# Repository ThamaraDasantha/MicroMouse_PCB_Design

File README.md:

# 🐭 Micromouse Robot – Custom PCB Design

This repository contains the **custom PCB design** for a Micromouse autonomous maze-solving robot. The design was inspired by the **Green Giant Micromouse**, a popular open-source project, and has been tailored to support modular, scalable, and competition-ready robotic development.

---

## 📦 Project Summary

Micromouse robots are small autonomous vehicles designed to solve mazes as quickly as possible. This PCB is the main controller board for such a robot, integrating motor drivers, sensors, power management, and microcontroller components in a compact footprint.

This design builds upon the **Green Giant Micromouse** architecture, with improvements for component sourcing, layout optimization, and modularity for further development.

---

## 🧠 Features & Specifications

| Category               | Description                                               |
|------------------------|-----------------------------------------------------------|
| **Microcontroller**    | STM32F4 / STM32F1 series (footprint supports both)        |
| **Motor Drivers**      | DRV8833 Dual H-Bridge for 2 DC motors                     |
| **Sensors**            | IR distance sensors (front, left, right, 45 digree) – 5 sensors |
| **Power System**       | 2-cell Li-ion with step-down regulator (5V and 3.3V rails)|
| **Connectivity**       | Serial debug headers, encoder inputs, IR TX/RX support    |
| **Form Factor**        | Compact 2-layer PCB, optimized for wheel/motor layout     |
| **Reference Design**   | Based on Green Giant Micromouse with custom adaptations   |

---

## 📐 PCB Design Overview

- Designed using **Eagle**
- Two-layer layout with clear separation of power and logic
- Silkscreen indicators for debugging and easy assembly
- Power and signal decoupling capacitors for noise stability
- Modular connector options for plugging in sensors and actuators

---

## 🧪 Testing & Next Steps

- Motor driver tested with small DC gear motors (30:1)
- Voltage rails tested with onboard regulators (5V and 3.3V)
- IR sensors and encoders interfaced with STM32 test code
- Future integration: PID motor control, maze-solving algorithm, IMU

---

## 📝 Acknowledgment

This design is heavily inspired by the [Green Giant Micromouse](https://github.com/davidtavarez/green-giant) project and adapted for educational and competitive use.

---

## 👨‍💻 Author

**Thamara Banneheka**  
Embedded Systems & Robotics Enthusiast  
📧 thamaradasantha@gmail.com  
🔗 [LinkedIn](https://www.linkedin.com/in/thamara-dasantha-banneheka/)

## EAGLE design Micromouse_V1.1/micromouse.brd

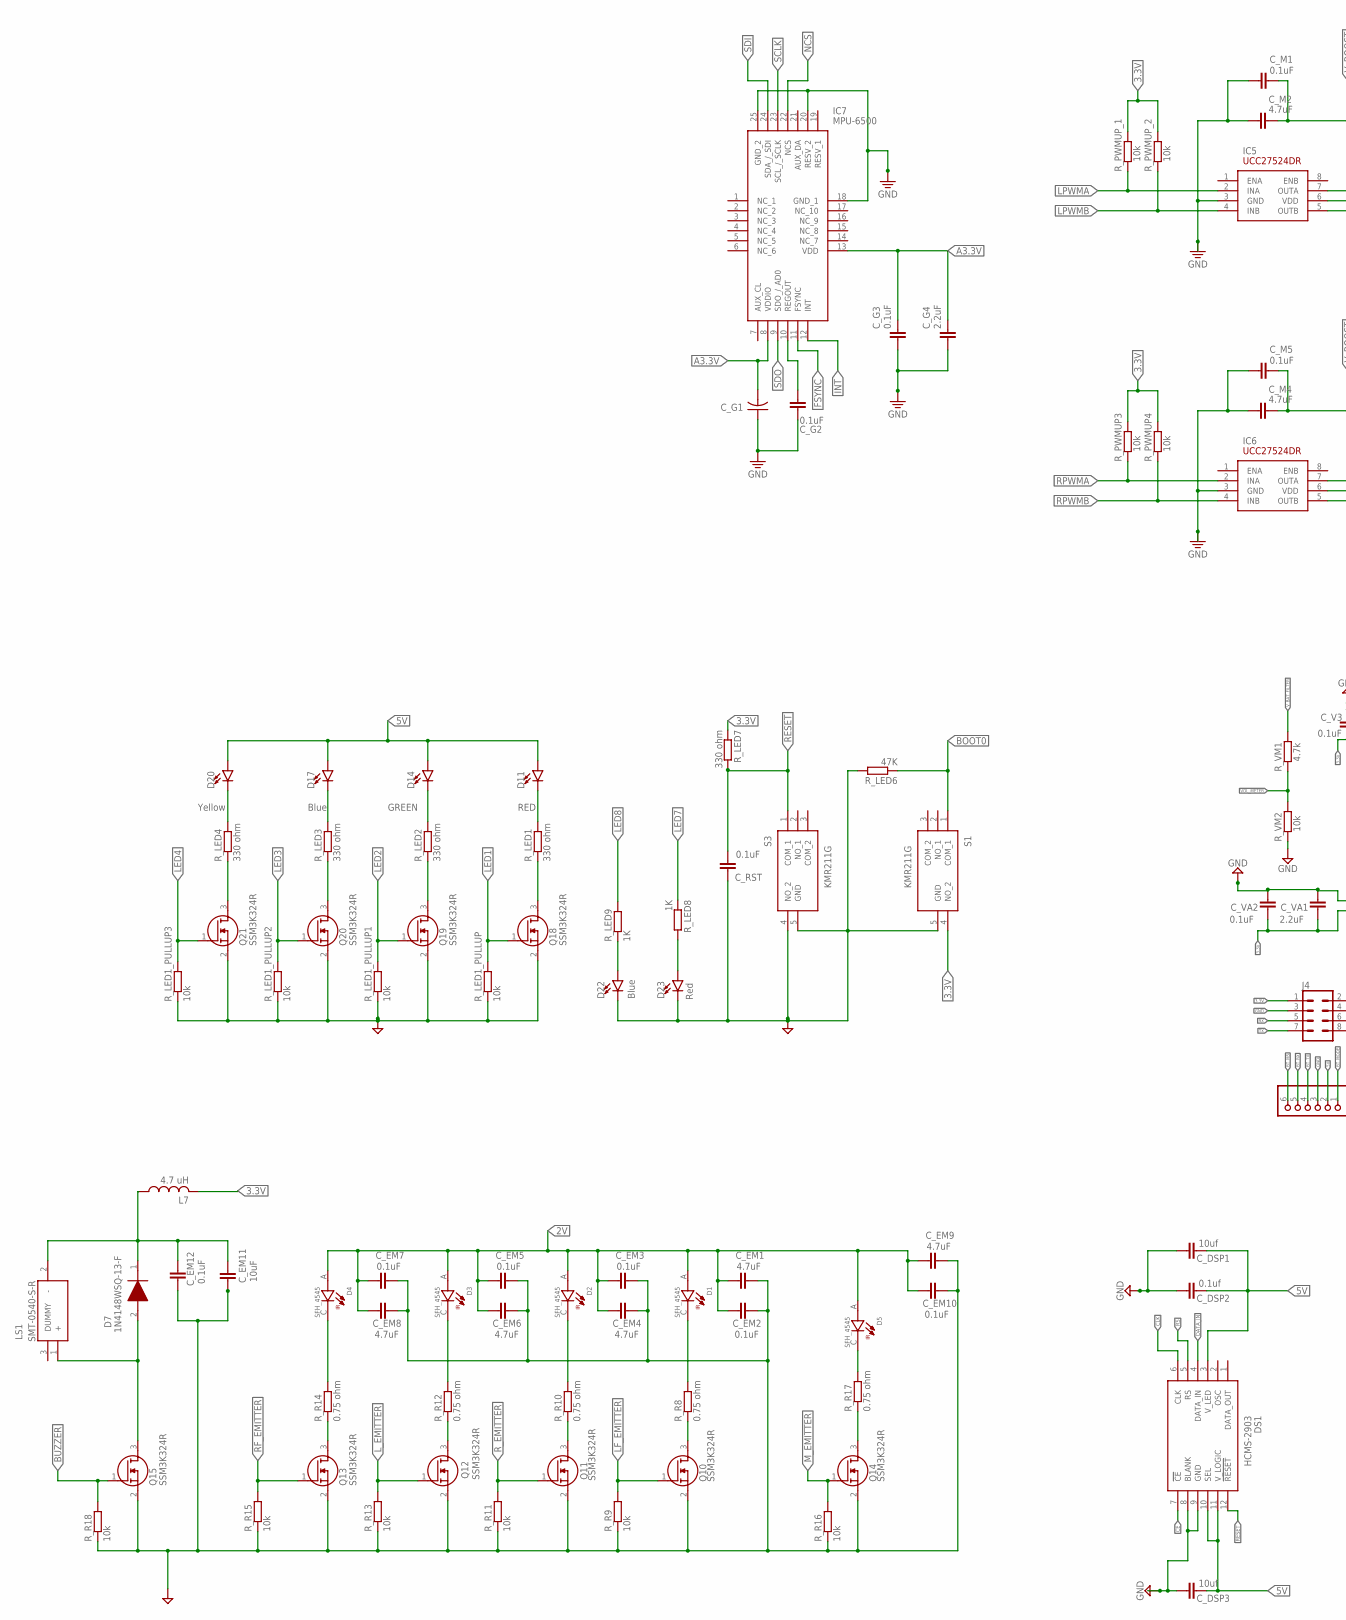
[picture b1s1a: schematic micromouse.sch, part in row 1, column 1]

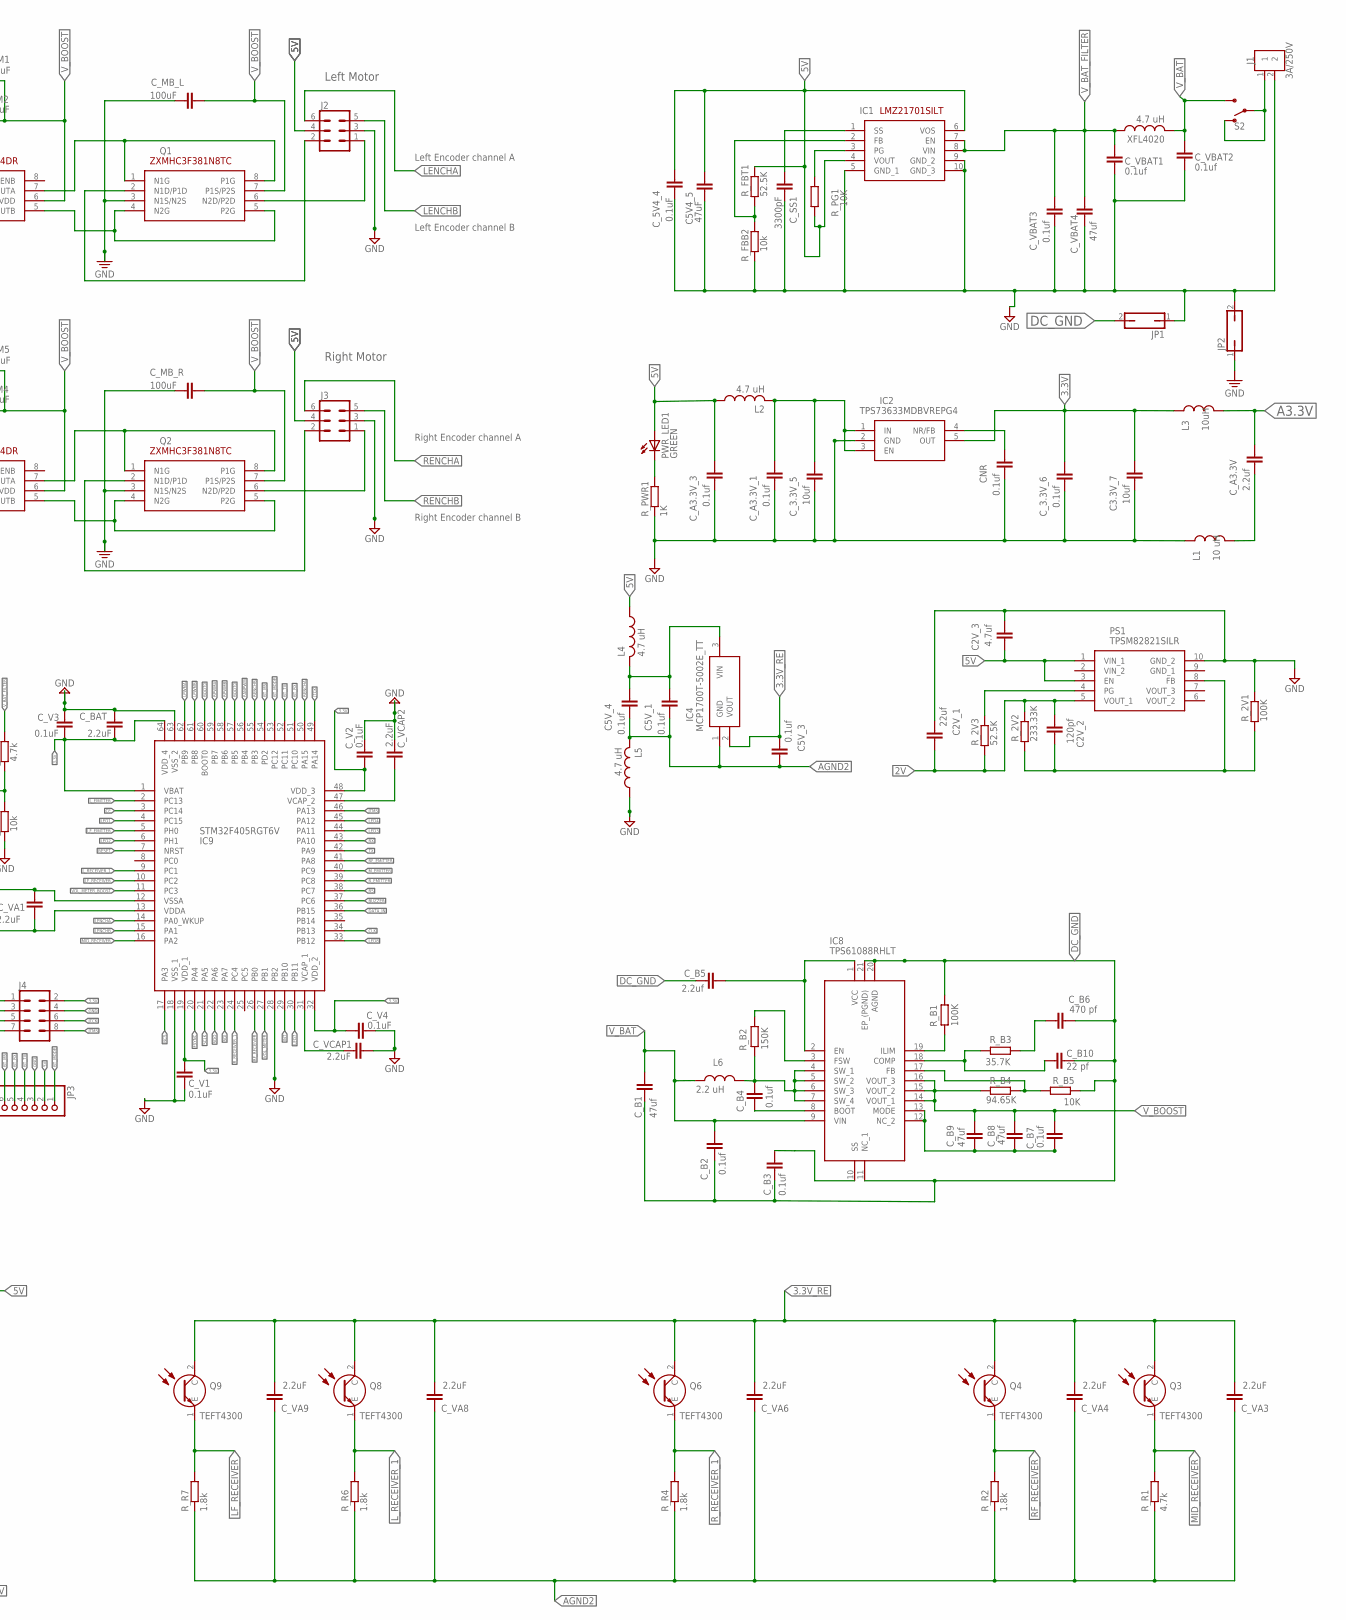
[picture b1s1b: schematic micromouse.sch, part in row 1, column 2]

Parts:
C2V_1: 22uf; CAPC2012X110
C2V_2: 120pf; CAPC2012X110
C2V_3: 4.7uf; CAPC2012X110
C3.3V_7: 10uf; CAPC2012X110
C5V4_5: 47uF; CAPC2012X110
C5V_1, C5V_3, C5V_4: 0.1uf; CAPC2012X110
CNR: 0.1uf; CAPC2012X110
C_3.3V_5: 10uf; CAPC2012X110
C_3.3V_6: 0.1uf; CAPC2012X110
C_5V4_4: 0.1uF; CAPC2012X110
C_A3.3V: 2.2uf; CAPC2012X110
C_A3.3V_1, C_A3.3V_3: 0.1uf; CAPC2012X110
C_B1, C_B8, C_B9: 47uf; CAPC2012X110
C_B2, C_B3, C_B4, C_B7: 0.1uf; CAPC2012X110
C_B5: 2.2uf; CAPC2012X110
C_B6: 470 pf; CAPC2012X110
C_B10: 22 pf; CAPC2012X110
C_BAT: 2.2uF; CAPC2012X110
C_DSP1, C_DSP3: 10uf; CAPC2012X110
C_DSP2: 0.1uf; CAPC2012X110
C_EM1, C_EM4, C_EM6, C_EM8, C_EM9: 4.7uF; CAPC2012X110
C_EM2, C_EM3, C_EM5, C_EM7, C_EM10, C_EM12: 0.1uF; CAPC2012X110
C_EM11: 10uF; CAPC2012X110
C_G1: 0.01uF; C0603K
C_G2, C_G3: 0.1uF; CAPC2012X110
C_G4: 2.2uF; CAPC2012X110
C_M1, C_M5: 0.1uF; CAPC2012X110
C_M2, C_M4: 4.7uF; CAPC2012X110
C_MB_L: 100uF; CAPC2012X110
C_MB_R: 100uF; CAPC2012X110
C_RST: 0.1uF; CAPC2012X110
C_SS1: 3300pF; CAPC2012X110
C_V1, C_V2, C_V3, C_V4: 0.1uF; CAPC2012X110
C_VA1, C_VA3, C_VA4, C_VA6, C_VA8, C_VA9: 2.2uF; CAPC2012X110
C_VA2: 0.1uF; CAPC2012X110
C_VBAT1, C_VBAT2, C_VBAT3: 0.1uf; CAPC2012X110
C_VBAT4: 47uf; CAPC2012X110
C_VCAP1, C_VCAP2: 2.2uF; CAPC2012X110
D1, D2, D3, D4, D5: SFH_4545; DIO_SFH_4545
D7: 1N4148WSQ-13-F; SOD2513X120N
D11, D14, D17, D20, D22, D23: LED0603; LED-0603
DS1: HCMS-2903; DIPS762W64P254L1778H508Q12N
IC1: LMZ21701SILT
IC2: TPS73633MDBVREPG4; SOT95P280X145-5N
IC4: MCP1700T-5002E_TT; SOT95P237X112-3N
IC5, IC6: UCC27524DR; SOIC127P600X175-8N
IC7: MPU-6500; QFN40P300X300X95-25N
IC8: TPS61088RHLT; BQ24031IRHLRQ1
IC9: STM32F405RGT6V; QFP50P1200X1200X160-64N
J1: 3A/250V; B2B-XH-A
J2, J3: MA03-2
J4: CONN_04X2; 2X4
JP1, JP2: JP1Q; JP1
JP3: PINHD-1X6; 1X06
L1: 10 uH; INDC2009X120
L2, L4, L5, L7: 4.7 uH; L4035M
L3: 10uH; INDC2009X120
L6: 2.2 uH; INDC2009X120
LS1: SMT-0540-S-R; SMT0540SR
PS1: TPSM82821SILR
PWR_LED1: GREEN; CHIPLED_0603
Q1, Q2: ZXMHC3F381N8TC; SOIC127P600X175-8N
Q3, Q4, Q6, Q8, Q9: TEFT4300
Q10, Q11, Q12, Q13, Q14, Q15, Q18, Q19, Q20, Q21: SSM3K324R; SOT95P240X88-3N
R_2V1: 100K; RESC1608X60
R_2V2: 233.33K; RESC1608X60
R_2V3: 52.5K; RESC1608X60
R_B1: 100K; RESC1608X60
R_B2: 150K; RESC1608X60
R_B3: 35.7K; RESC1608X60
R_B4: 94.65K; RESC1608X60
R_B5: 10K; RESC1608X60
R_FBB2: 10k; RESC1608X60
R_FBT1: 52.5K; RESC1608X60
R_LED1, R_LED2, R_LED3, R_LED4, R_LED7: 330 ohm; RESC1608X60
R_LED1_PULLUP, R_LED1_PULLUP1, R_LED1_PULLUP2, R_LED1_PULLUP3: 10k; RESC1608X60
R_LED6: 47K; RESC1608X60
R_LED8, R_LED9: 1K; RESC1608X60
R_PG1: 10K; RESC1608X60
R_PWMUP3, R_PWMUP4: 10k; RESC1608X60
R_PWMUP_1, R_PWMUP_2: 10k; RESC1608X60
R_PWR1: 1K; RESC1608X60
R_R1: 4.7k; RESC1608X60
R_R2, R_R4, R_R6, R_R7: 1.8k; RESC1608X60
R_R8, R_R10, R_R12, R_R14, R_R17: 0.75 ohm; RESC1608X60
R_R9, R_R11, R_R13, R_R15, R_R16, R_R18: 10k; RESC1608X60
R_VM1: 4.7k; RESC1608X60
R_VM2: 10k; RESC1608X60
S1, S3: KMR211G
S2: SWITCH-SPDT-PTH-11.6X4.0MM; SWITCH_SPDT_PTH_11.6X4.0MM
XFL4020: 4.7 uH; L4035M

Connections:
2V: C2V_1.2, C2V_2.1, C_EM1.1, C_EM2.1, C_EM3.1, C_EM4.1, C_EM5.1, C_EM6.1, C_EM7.1, C_EM8.1, C_EM9.1, C_EM10.1, D1.A, D2.A, D3.A, D4.A, D5.A, PS1.5 (VOUT_1), R_2V2.2, R_2V3.1
3.3V: C3.3V_7.2, C_3.3V_6.2, C_BAT.1, C_V1.2, C_V2.1, C_V3.1, C_V4.1, C_VA1.1, C_VA2.1, IC2.5 (OUT), IC9.1 (VBAT), IC9.13 (VDDA), IC9.19 (VDD_1), IC9.32 (VDD_2), IC9.48 (VDD_3), IC9.64 (VDD_4), J4.1, J4.2, L3.1, L7.2, R_LED7.1, R_PWMUP3.2, R_PWMUP4.2, R_PWMUP_1.2, R_PWMUP_2.2, S1.4 (NO_2)
3.3V_RE: C5V_3.1, C_VA3.1, C_VA4.1, C_VA6.1, C_VA8.1, C_VA9.1, IC4.2 (VOUT), Q3.2 (C), Q4.2 (C), Q6.2 (C), Q8.2 (C), Q9.2 (C)
5V: C2V_3.2, C5V4_5.1, C_5V4_4.2, C_A3.3V_3.2, C_DSP1.1, C_DSP2.1, C_DSP3.1, D11.A, D14.A, D17.A, D20.A, DS1.3 (V_LED), DS1.10 (SEL), DS1.11 (V_LOGIC), IC1.4 (VOUT), IC1.6 (VOS), J2.4, J3.4, JP3.2, L2.1, L4.1, PS1.1 (VIN_1), PS1.3 (EN), PWR_LED1.A, R_FBT1.2, R_PG1.1
A3.3V: C_A3.3V.2, C_G1.2, C_G3.1, C_G4.1, IC7.8 (VDDIO), IC7.13 (VDD), L3.2
AGND2: C5V_1.1, C5V_3.2, C5V_4.1, C_VA3.2, C_VA4.2, C_VA6.2, C_VA8.2, C_VA9.2, IC4.1 (GND), L5.2, R_R1.1, R_R2.1, R_R4.1, R_R6.1, R_R7.1
BOOT0: IC9.57 (PB5), IC9.60 (BOOT0), R_LED6.1, S1.1 (COM_1)
BT_MODE: IC9.53 (PC12), JP3.1
BT_MS: IC9.54 (PD2), JP3.6
BT_RX: IC9.51 (PC10), JP3.5
BT_TX: IC9.52 (PC11), JP3.4
BUZZER: IC9.37 (PC6), Q15.1 (G), R_R18.2
CE: DS1.7 (!CE), IC9.3 (PC14)
CLK: DS1.6 (CLK), IC9.34 (PB13)
DATA_IN: DS1.4 (DATA_IN), IC9.36 (PB15)
DC_GND: C_B1.2, C_B2.2, C_B3.1, C_B5.1, C_B6.1, C_B10.1, IC8.11 (NC_1), IC8.20 (AGND), IC8.21 (EP_(PGND)), JP1.2, R_B1.1, R_B5.1
FANPWM: IC9.56 (PB4)
FSYNC: IC7.11 (FSYNC), IC9.20 (PA4)
GND: C2V_1.1, C2V_3.1, C3.3V_7.1, C5V4_5.2, CNR.1, C_3.3V_5.1, C_3.3V_6.1, C_5V4_4.1, C_A3.3V_1.1, C_A3.3V_3.1, C_BAT.2, C_DSP1.2, C_DSP2.2, C_DSP3.2, C_EM1.2, C_EM2.2, C_EM3.2, C_EM4.2, C_EM5.2, C_EM6.2, C_EM7.2, C_EM8.2, C_EM9.2, C_EM10.2, C_EM11.2, C_EM12.1, C_M1.2, C_M2.1, C_M4.1, C_M5.2, C_MB_L.1, C_MB_R.1, C_RST.2, C_SS1.1, C_V1.1, C_V2.2, C_V3.2, C_V4.2, C_VA1.2, C_VA2.2, C_VBAT1.2, C_VBAT2.2, C_VBAT3.1, C_VBAT4.1, C_VCAP1.1, C_VCAP2.2, D22.C, D23.C, DS1.8 (BLANK), DS1.9 (GND), IC1.5 (GND_1), IC1.9 (GND_2), IC1.10 (GND_3), IC2.2 (GND), IC5.3 (GND), IC6.3 (GND), IC9.12 (VSSA), IC9.18 (VSS_1), IC9.28 (PB2), IC9.63 (VSS_2), J1.2, J2.3, J3.3, J4.3, J4.4, JP1.1, JP2.1, JP2.2, JP3.3, L1.1, L5.1, PS1.10 (GND_2), Q1.3 (N1S/N2S), Q2.3 (N1S/N2S), Q10.2 (S), Q11.2 (S), Q12.2 (S), Q13.2 (S), Q14.2 (S), Q15.2 (S), Q18.2 (S), Q19.2 (S), Q20.2 (S), Q21.2 (S), R_2V1.2, R_FBB2.1, R_LED1_PULLUP.1, R_LED1_PULLUP1.1, R_LED1_PULLUP2.1, R_LED1_PULLUP3.1, R_LED6.2, R_PWR1.1, R_R9.1, R_R11.1, R_R13.1, R_R15.1, R_R16.1, R_R18.1, R_VM2.1, S1.5 (GND), S3.4 (NO_2), S3.5 (GND)
INT: IC7.12 (INT), IC9.29 (PB10)
JTCK: IC9.49 (PA14), J4.6
JTMS: IC9.46 (PA13), J4.8
LED1: IC9.4 (PC15), Q18.1 (G), R_LED1_PULLUP.2
LED2: IC9.6 (PH1), Q19.1 (G), R_LED1_PULLUP1.2
LED3: IC9.44 (PA11), Q20.1 (G), R_LED1_PULLUP2.2
LED4: IC9.45 (PA12), Q21.1 (G), R_LED1_PULLUP3.2
LED7: IC9.30 (PB11), R_LED8.1
LED8: IC9.33 (PB12), R_LED9.2
LENCHA: IC9.14 (PA0_WKUP), J2.6
LENCHB: IC9.15 (PA1), J2.5
LF_EMITTER: IC9.5 (PH0), Q10.1 (G), R_R9.2
LF_RECEIVER: IC9.10 (PC2), Q9.1 (E), R_R7.2
LPWMA: IC5.2 (INA), IC9.62 (PB9), R_PWMUP_1.1
LPWMB: IC5.4 (INB), IC9.61 (PB8), R_PWMUP_2.1
L_EMITTER: IC9.2 (PC13), Q12.1 (G), R_R13.2
L_RECEIVER_1: IC9.9 (PC1), Q8.1 (E), R_R6.2
MID_RECEIVER: IC9.16 (PA2), Q3.1 (E), R_R1.2
M_EMITTER: IC9.40 (PC9), Q14.1 (G), R_R16.2
unnamed: C_SS1.2, IC1.1 (SS)
unnamed: IC5.7 (OUTA), Q1.1 (N1G), Q1.8 (P1G)
unnamed: IC1.3 (PG), R_PG1.2
unnamed: C_3.3V_5.2, C_A3.3V_1.2, IC2.1 (IN), IC2.3 (EN), L2.2
unnamed: PWR_LED1.C, R_PWR1.2
unnamed: IC1.2 (FB), R_FBB2.2, R_FBT1.1
unnamed: J1.1, S2.1 (O), S2.2
unnamed: CNR.2, IC2.4 (NR/FB)
unnamed: IC6.7 (OUTA), Q2.1 (N1G), Q2.8 (P1G)
unnamed: C5V_1.2, C5V_4.2, IC4.3 (VIN), L4.2
unnamed: C_A3.3V.1, L1.2
unnamed: IC6.5 (OUTB), Q2.4 (N2G), Q2.5 (P2G)
unnamed: IC5.5 (OUTB), Q1.4 (N2G), Q1.5 (P2G)
unnamed: J3.2, Q2.2 (N1D/P1D)
unnamed: J2.2, Q1.2 (N1D/P1D)
unnamed: J2.1, Q1.6 (N2D/P2D)
unnamed: J3.1, Q2.6 (N2D/P2D)
unnamed: IC7.18 (GND_1), IC7.20 (RESV_2), IC7.25 (GND_2)
unnamed: C_G3.2, C_G4.2
unnamed: C_G2.1, IC7.10 (REGOUT)
unnamed: C_G1.1, C_G2.2
unnamed: C_B3.2, IC8.10 (SS)
unnamed: C_B4.2, IC8.8 (BOOT)
unnamed: D1.C, R_R8.2
unnamed: C_B4.1, IC8.4 (SW_1), IC8.5 (SW_2), IC8.6 (SW_3), IC8.7 (SW_4), L6.2, R_B2.1
unnamed: IC8.19 (ILIM), R_B1.2
unnamed: C_B10.2, IC8.18 (COMP), R_B3.2
unnamed: IC8.3 (FSW), R_B2.2
unnamed: C_B5.2, IC8.1 (VCC), IC8.2 (EN)
unnamed: Q10.3 (D), R_R8.1
unnamed: C_B6.2, R_B3.1
unnamed: IC8.17 (FB), R_B4.1, R_B5.2
unnamed: Q14.3 (D), R_R17.1
unnamed: C_B7.2, C_B8.2, C_B9.2, IC8.12 (NC_2), IC8.13 (MODE)
unnamed: D5.C, R_R17.2
unnamed: D2.C, R_R10.2
unnamed: Q11.3 (D), R_R10.1
unnamed: C2V_2.2, PS1.8 (FB), R_2V1.1, R_2V2.1
unnamed: D7.2 (A), LS1.1 (+), Q15.3 (D)
unnamed: C_EM11.1, C_EM12.2, D7.1 (K), L7.1, LS1.2 (-)
unnamed: D3.C, R_R12.2
unnamed: Q12.3 (D), R_R12.1
unnamed: PS1.4 (PG), R_2V3.2
unnamed: C_VCAP2.1, IC9.47 (VCAP_2)
unnamed: D4.C, R_R14.2
unnamed: Q13.3 (D), R_R14.1
unnamed: C_VCAP1.2, IC9.31 (VCAP_1)
unnamed: Q18.3 (D), R_LED1.1
unnamed: D11.C, R_LED1.2
unnamed: Q19.3 (D), R_LED2.1
unnamed: D14.C, R_LED2.2
unnamed: D22.A, R_LED9.1
unnamed: Q20.3 (D), R_LED3.1
unnamed: D17.C, R_LED3.2
unnamed: D23.A, R_LED8.2
unnamed: Q21.3 (D), R_LED4.1
unnamed: D20.C, R_LED4.2
NCS: IC7.22 (NCS), IC9.17 (PA3)
RENCHA: IC9.50 (PA15), J3.6
RENCHB: IC9.55 (PB3), J3.5
RESET: C_RST.1, DS1.12 (!RESET), IC9.7 (NRST), R_LED7.2, S3.1 (COM_1)
RF_EMITTER: IC9.41 (PA8), Q13.1 (G), R_R15.2
RF_RECEIVER: IC9.26 (PB0), Q4.1 (E), R_R2.2
RPWMA: IC6.2 (INA), IC9.59 (PB7), R_PWMUP3.1
RPWMB: IC6.4 (INB), IC9.58 (PB6), R_PWMUP4.1
RS: DS1.5 (RS), IC9.38 (PC7)
RX: IC9.43 (PA10), J4.5
R_EMITTER: IC9.39 (PC8), Q11.1 (G), R_R11.2
R_RECEIVER_1: IC9.24 (PC4), Q6.1 (E), R_R4.2
SCLK: IC7.23 (SCL_/_SCLK), IC9.21 (PA5)
SDI: IC7.24 (SDA_/_SDI), IC9.23 (PA7)
SDO: IC7.9 (SDO_/_AD0), IC9.22 (PA6)
TX: IC9.42 (PA9), J4.7
VOL_METER: IC9.27 (PB1), R_VM1.1, R_VM2.2
VOL_METER_BOOST: IC9.11 (PC3)
V_BAT: C_B1.1, C_B2.1, C_VBAT2.1, IC8.9 (VIN), L6.1, S2.3 (S), XFL4020.2
V_BAT_FILTER: C_VBAT1.1, C_VBAT3.2, C_VBAT4.2, IC1.7 (EN), IC1.8 (VIN), R_VM1.2, XFL4020.1
V_BOOST: C_B7.1, C_B8.1, C_B9.1, C_M1.1, C_M2.2, C_M4.2, C_M5.1, C_MB_L.2, C_MB_R.2, IC5.6 (VDD), IC6.6 (VDD), IC8.14 (VOUT_1), IC8.15 (VOUT_2), IC8.16 (VOUT_3), Q1.7 (P1S/P2S), Q2.7 (P1S/P2S), R_B4.2

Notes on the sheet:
Left Motor
Right Motor
RED
GREEN
Blue
Yellow
Red
Right Encoder channel A
Right Encoder channel B
Left Encoder channel B
Left Encoder channel A

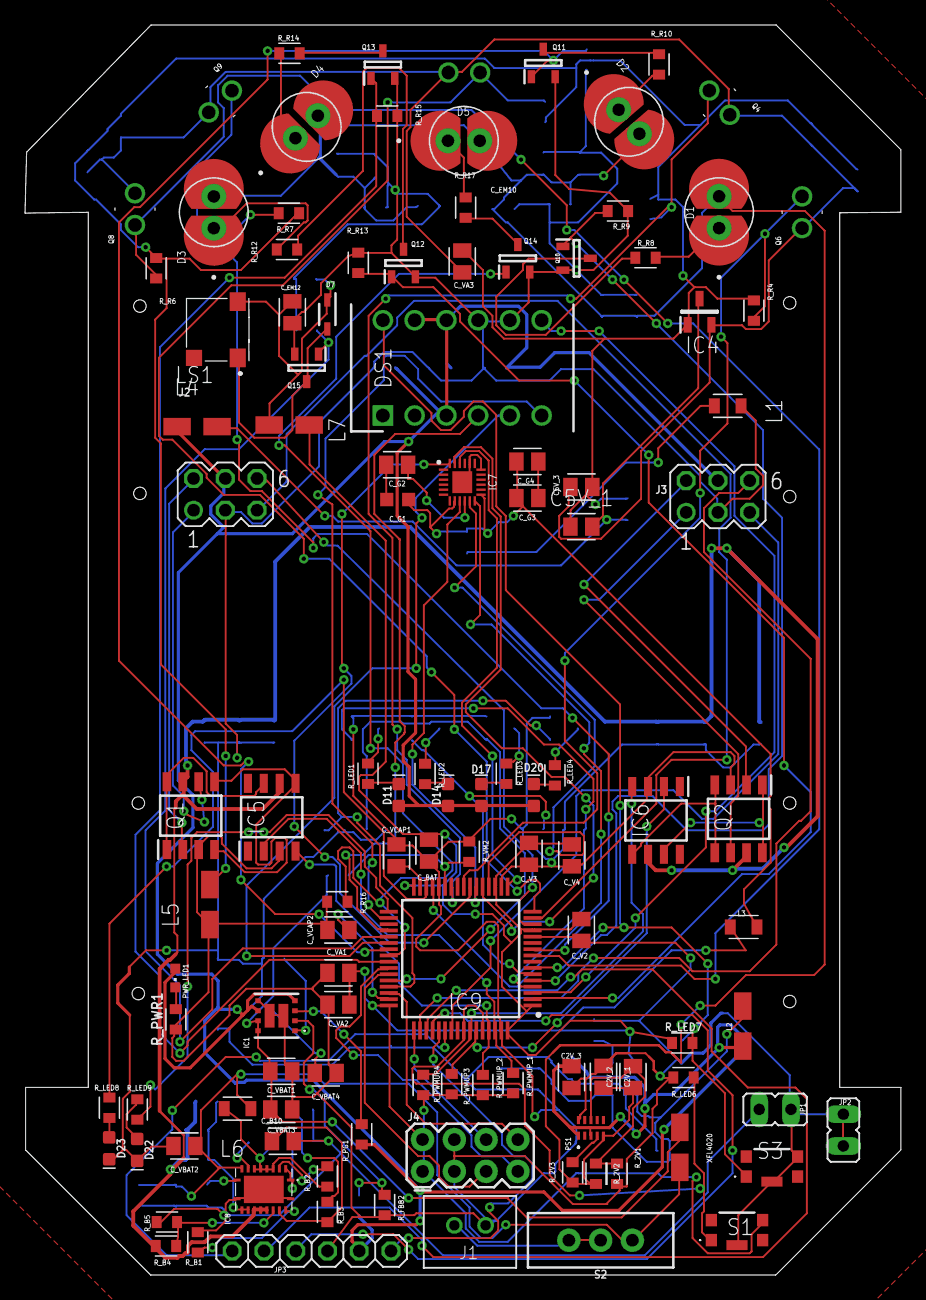
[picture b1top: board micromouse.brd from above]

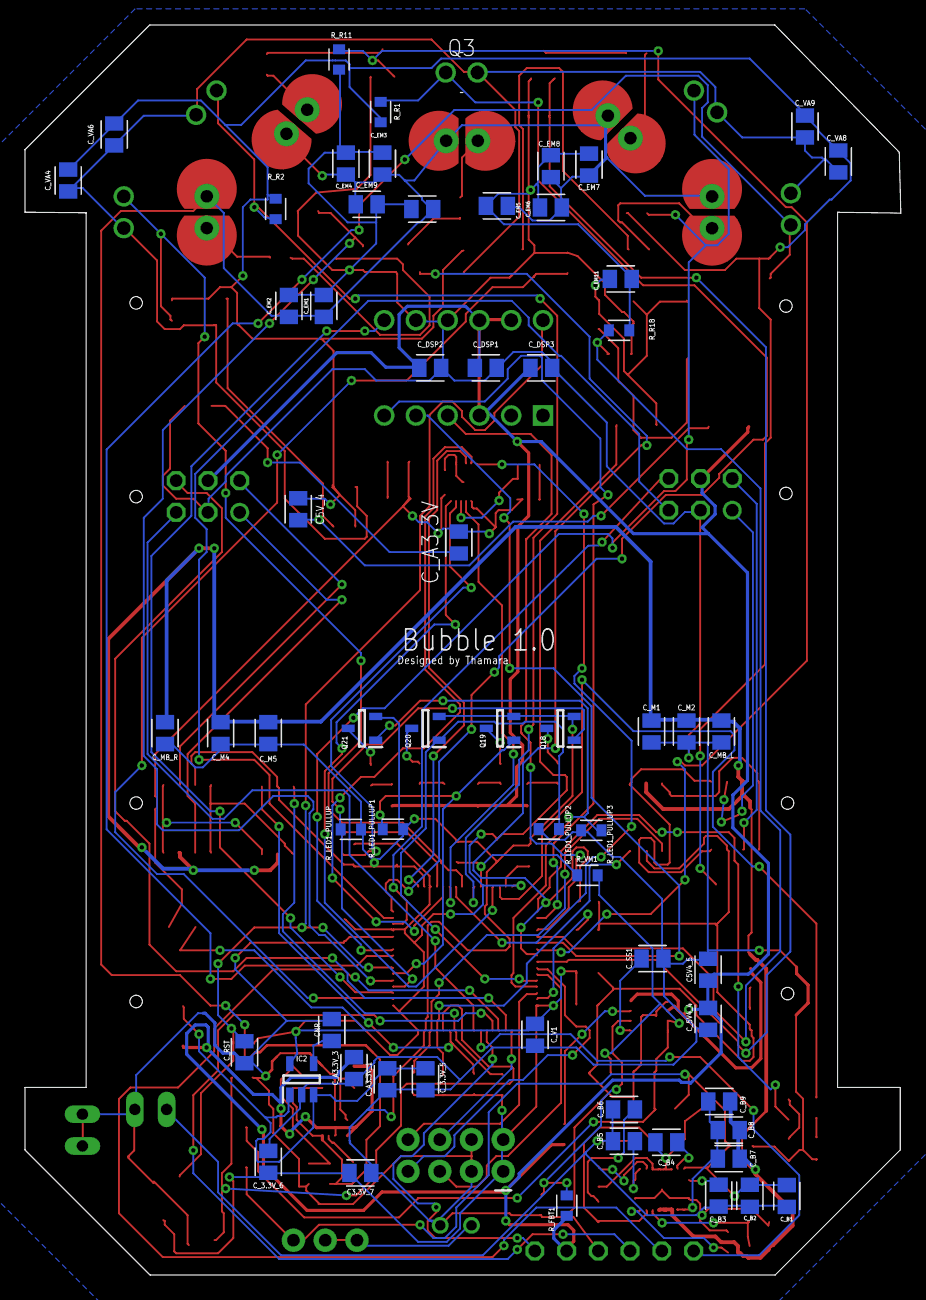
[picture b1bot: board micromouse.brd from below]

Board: 2 copper layers, 70.0 x 100.0 mm, 175 parts (62 on the bottom side), 114 nets.

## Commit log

2025-06-20 mainfiles

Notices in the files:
parts and their libraries:
SparkFun-Switches: Licensing: Creative Commons ShareAlike 4.0 International - https://creativecommons.org/licenses/by-sa/4.0
